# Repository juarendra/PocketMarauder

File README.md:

# PocketMarauder

Perangkat pentest saku: **ESP32-WROOM-32D + OLED 128x64 (SSD1306) + 4 tombol**, berjalan di firmware fork [ESP32Marauder](https://github.com/Spacehuhn/ESP32Marauder) dengan 4 fitur pentest tambahan yang di-build khusus untuk target `POCKET_MARAUDER`.

```
[ OLED 128x64 ]   [ ESP32-WROOM-32D ]
  I2C (IO21/22)     [ A ] [ B ] [ C ] [ D ]   (IO35/32/33/25)
                    Bat: LiPo via TP4056 (IO34)   LED aktif: IO19
```

> **Gambar hardware**: [`docs/images/hardware-placeholder.png`](docs/images/hardware-placeholder.png) — masih placeholder; foto/diagram asli menyusul.

## Fitur

### Firmware bawaan ESP32Marauder (v1.17.0)
- **WiFi** — sniffers (beacon/probe/deauth/EAPOL), scanners (channel analyzer, PineScan, Fox Hunt), attacks (deauth, beacon spam, Karma, Evil Portal, SAE commit, dst.), packet monitor.
- **Bluetooth** — sniffers (BLE scan, FindMy/Airtag, CC skimmer), attacks (Sour Apple, BLE spam, Spoof Airtag).
- **OLED natif** — menu + status bar + persentase baterai, tanpa TFT.
- **Baterai** — ADC IO34 (divider 5.02×), ditampilkan % di status bar.
- **LED aktivitas** — hijau di IO19, menyala saat scan/attack aktif.

### Fitur tambahan (khusus PocketMarauder)
| Fitur | Menu | Fungsi |
|---|---|---|
| **WPS Scan** | WiFi → Sniffers | Pasif: deteksi AP yang mengiklankan WPS, flag `PIN-PRONE` / `LOCKED` |
| **Probe Spam** | WiFi → Attacks | Flood probe request dengan SSID acak |
| **Roam Bait** | WiFi → Attacks | Beacon palsu dengan IE 802.11r (MD) + 802.11k (RM caps) |
| **GATT Explore** | BT → Attacks | Koneksi BLE, enumerasi services/characteristics/values |

Detail penggunaan per fitur: [`docs/USER_MANUAL.md`](docs/USER_MANUAL.md).

## Hardware

| Komponen | Detail |
|---|---|
| MCU | ESP32-WROOM-32D (2.4 GHz WiFi + BLE) |
| Tampilan | SSD1306 OLED 128x64 mono, I2C addr `0x3C` (SDA=IO21, SCL=IO22) |
| Tombol | A=Up (IO35), B=Left/Back (IO32), C=Center/Select (IO33), D=Down (IO25) — active-low, pull-up 10k |
| Baterai | LiPo via charger TP4056 + proteksi; tegangan dibaca IO34 (ADC1_CH6, divider 10k/40.2k) |
| LED | Hijau IO19 (active-low), indikasi aktivitas scan |
| Antena | U.FL — gunakan antena tersambung untuk hasil scan maksimal |

PCB/EAGLE source: [`PCB/EAGLE/`](PCB/EAGLE/).

## Build & Flash

Prasyarat: [PlatformIO](https://platformio.org) CLI + Python 3.

```bash
cd firmware
python -m platformio run -e pocket_marauder        # build (~60 detik)
python -m platformio run -e pocket_marauder -t upload   # flash (butuh USB flasher)
python -m platformio run -e pocket_marauder -t monitor  # serial monitor
```

Build terakhir: **GREEN** — Flash 81.7% (1605679/1966080), RAM 24.9% (81724/327680).

Output: `firmware.bin` (app) + `firmware.factory.bin` (gabungan bootloader + partisi + app).

## Struktur Repo

```
firmware/            firmware (fork ESP32Marauder, target POCKET_MARAUDER)
  esp32_marauder/    source utama
  tools/             build helpers PlatformIO
  installer/         build pipeline installer
PCB/EAGLE/           source PCB (schematic)
docs/
  USER_MANUAL.md     manual pengguna (lengkap)
  images/            simulasi tampilan OLED + placeholder hardware
  plans/             rencana kerja internal
CHANGELOG.md         log perubahan
```

## Lisensi

[GNU GPL v3](LICENSE). Fork dari ESP32Marauder (upstream juga GPLv3).

## Disclaimer

Alat ini untuk **pengujian keamanan yang sah** (lab sendiri, jaringan sendiri, atau dengan izin tertulis pemilik jaringan). Penggunaan di jaringan yang tidak kamu miliki tanpa izin adalah **ilegal** di hampir semua yurisdiksi. Pengguna bertanggung jawab penuh atas perbuatannya.

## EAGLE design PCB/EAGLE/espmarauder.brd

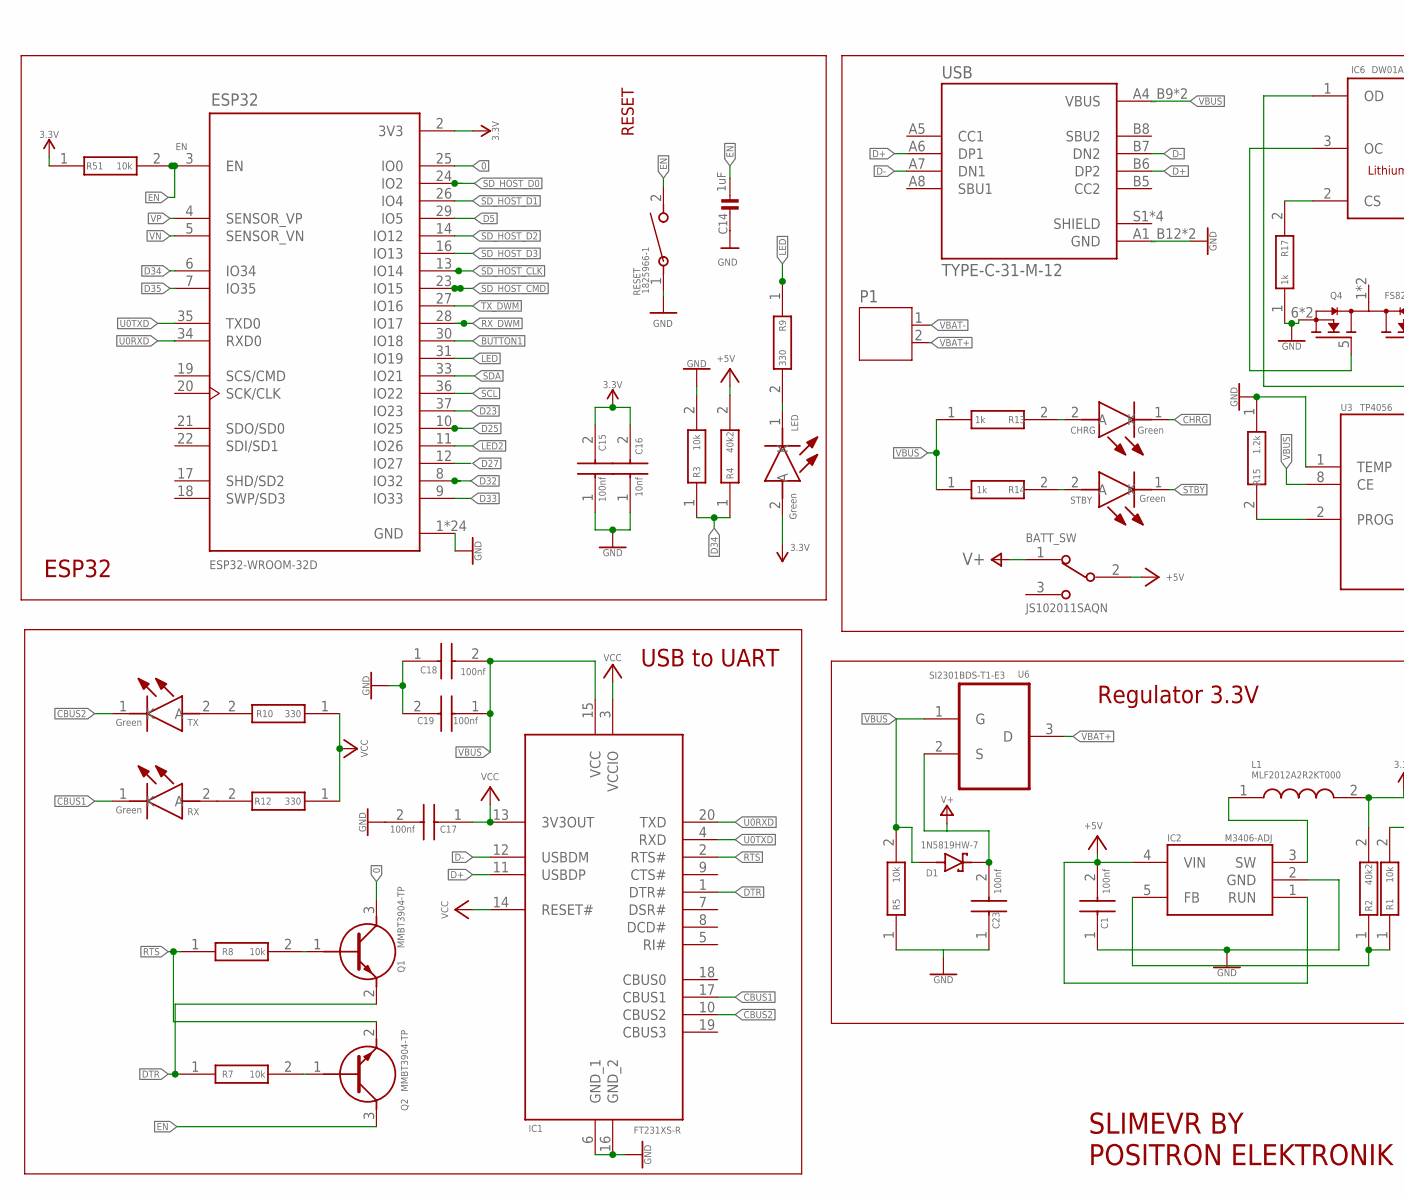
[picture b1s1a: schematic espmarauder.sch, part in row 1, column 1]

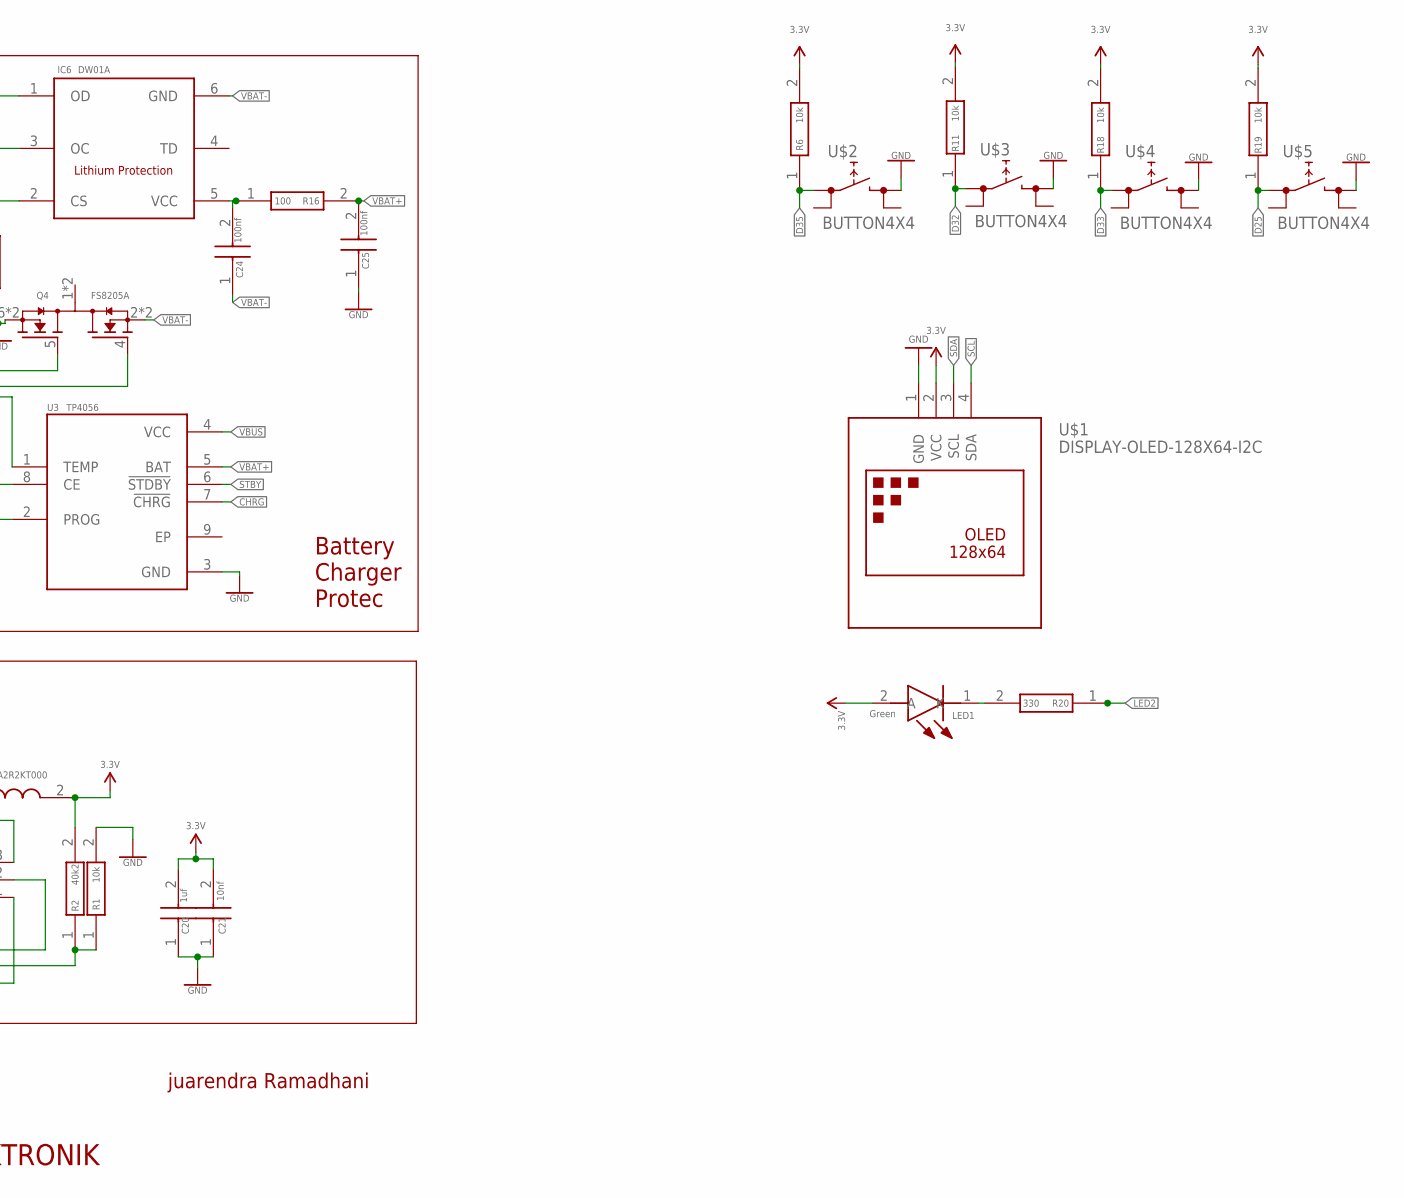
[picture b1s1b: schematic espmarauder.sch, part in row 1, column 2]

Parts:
BATT_SW: JS102011SAQN; SW_JS102011SAQN
C1, C15, C17, C18, C19, C23, C24, C25: 100nf; CAPC1608X87N
C14: 1uF; 0603
C16, C21: 10nf; CAPC1608X87N
C20: 1uf; CAPC1608X87N
CHRG: Green; LEDC2012X80N
D1: 1N5819HW-7; SOD3715X145N
ESP32: ESP32-WROOM-32D; MODULE_ESP32-WROOM-32D
IC1: FT231XS-R; SOP64P599X175-20N
IC2: M3406-ADJ; SOT95P280X100-5N
IC6: DW01A; SOT23-6
L1: MLF2012A2R2KT000; INDC2012X105N
LED, LED1: Green; LEDC2012X80N
P1: JST-PH2
Q1, Q2: MMBT3904-TP; SI2305TP
Q4: FS8205A; SOP65P640X120-8N
R1, R3, R5, R6, R7, R8, R11, R18, R19, R51: 10k; RESC1608X55N
R2, R4: 40k2; RESC1608X55N
R9, R10, R12, R20: 330; ERJH3
R13, R14, R17: 1k; RESC1608X55N
R15: 1.2k; RESC1608X55N
R16: 100; RESC1608X55N
RESET: 1825966-1; SWDIP2_256X170P100
RX: Green; LEDC2012X80N
STBY: Green; LEDC2012X80N
TX: Green; LEDC2012X80N
U3: TP4056; SOP127P600X175-9N
U6: SI2301BDS-T1-E3; SOT95P237X112-3N
U$1: DISPLAY-OLED-128X64-I2C
U$2, U$3, U$4, U$5: BUTTON4X4
USB: TYPE-C-31-M-12; HRO_TYPE-C-31-M-12

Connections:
0: ESP32.25 (IO0), Q1.3 (C)
3.3V: C15.2, C16.2, C20.2, C21.2, ESP32.2 (3V3), L1.2, LED.2 (A), LED1.2 (A), R2.2, R6.2, R11.2, R18.2, R19.2, R51.1, U$1.2 (VCC)
+5V: BATT_SW.2, C1.2, IC2.1 (RUN), IC2.4 (VIN), R4.2
BUTTON1: ESP32.30 (IO18)
CBUS1: IC1.17 (CBUS1), RX.1 (K)
CBUS2: IC1.10 (CBUS2), TX.1 (K)
CHRG: CHRG.1 (K), U3.7 (!CHRG)
D5: ESP32.29 (IO5)
D23: ESP32.37 (IO23)
D25: ESP32.10 (IO25), R19.1, U$5.1
D27: ESP32.12 (IO27)
D32: ESP32.8 (IO32), R11.1, U$3.1
D33: ESP32.9 (IO33), R18.1, U$4.1
D34: ESP32.6 (IO34), R3.1, R4.1
D35: ESP32.7 (IO35), R6.1, U$2.1
D+: IC1.11 (USBDP), USB.A6 (DP1), USB.B6 (DP2)
D-: IC1.12 (USBDM), USB.A7 (DN1), USB.B7 (DN2)
DTR: IC1.1 (DTR#), Q1.2 (E), R7.1
EN: C14.1, ESP32.3 (EN), Q2.3 (C), R51.2, RESET.2
GND: C1.1, C14.2, C15.1, C16.1, C17.2, C18.1, C19.2, C20.1, C21.1, C23.1, C25.1, ESP32.1 (GND), ESP32.15 (GND), ESP32.38 (GND), ESP32.39_1 (GND), ESP32.39_2 (GND), ESP32.39_3 (GND), ESP32.39_4 (GND), ESP32.39_5 (GND), ESP32.39_6 (GND), ESP32.39_7 (GND), ESP32.39_8 (GND), ESP32.39_9 (GND), ESP32.39_10 (GND), ESP32.39_11 (GND), ESP32.39_12 (GND), ESP32.39_13 (GND), ESP32.39_14 (GND), ESP32.39_15 (GND), ESP32.39_16 (GND), ESP32.39_17 (GND), ESP32.39_18 (GND), ESP32.39_19 (GND), ESP32.39_20 (GND), ESP32.39_21 (GND), IC1.6 (GND_1), IC1.16 (GND_2), IC2.2 (GND), Q4.6 (S2), Q4.7 (S2), R1.2, R3.2, R5.1, R15.1, R17.1, RESET.1, U3.1 (TEMP), U3.3 (GND), U$1.1 (GND), U$2.3, U$3.3, U$4.3, U$5.3, USB.A1_B12 (GND), USB.B1_A12 (GND)
LED: ESP32.31 (IO19), R9.1
LED2: ESP32.11 (IO26), R20.1
unnamed: IC2.3 (SW), L1.1
unnamed: LED.1 (K), R9.2
unnamed: IC2.5 (FB), R1.1, R2.1
unnamed: LED1.1 (K), R20.2
unnamed: Q2.1 (B), R7.2
unnamed: Q1.1 (B), R8.2
unnamed: R12.2, RX.2 (A)
unnamed: R10.2, TX.2 (A)
unnamed: CHRG.2 (A), R13.2
unnamed: R14.2, STBY.2 (A)
unnamed: R15.2, U3.2 (PROG)
unnamed: C24.2, IC6.5 (VCC), R16.1
unnamed: IC6.1 (OD), Q4.4 (G1)
unnamed: IC6.2 (CS), R17.2
unnamed: IC6.3 (OC), Q4.5 (G2)
RTS: IC1.2 (RTS#), Q2.2 (E), R8.1
RX_DWM: ESP32.28 (IO17)
SCL: ESP32.36 (IO22), U$1.4 (SDA)
SDA: ESP32.33 (IO21), U$1.3 (SCL)
SD_HOST_CLK: ESP32.13 (IO14)
SD_HOST_CMD: ESP32.23 (IO15)
SD_HOST_D0: ESP32.24 (IO2)
SD_HOST_D1: ESP32.26 (IO4)
SD_HOST_D2: ESP32.14 (IO12)
SD_HOST_D3: ESP32.16 (IO13)
STBY: STBY.1 (K), U3.6 (!STDBY)
TX_DWM: ESP32.27 (IO16)
U0RXD: ESP32.34 (RXD0), IC1.20 (TXD)
U0TXD: ESP32.35 (TXD0), IC1.4 (RXD)
V+: BATT_SW.1, C23.2, D1.C (K), U6.2 (S)
VBAT+: C25.2, P1.2, R16.2, U3.5 (BAT), U6.3 (D)
VBAT-: C24.1, IC6.6 (GND), P1.1, Q4.2 (S1), Q4.3 (S1)
VBUS: C18.2, C19.1, D1.A, IC1.15 (VCC), R5.2, R13.1, R14.1, U3.4 (VCC), U3.8 (CE), U6.1 (G), USB.A4_B9 (VBUS), USB.B4_A9 (VBUS)
VCC: C17.1, IC1.3 (VCCIO), IC1.13 (3V3OUT), IC1.14 (RESET#), R10.1, R12.1
VN: ESP32.5 (SENSOR_VN)
VP: ESP32.4 (SENSOR_VP)

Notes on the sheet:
RESET
ESP32
USB to UART
Battery Charger Protec
Regulator 3.3V
SLIMEVR BY POSITRON ELEKTRONIK
juarendra Ramadhani

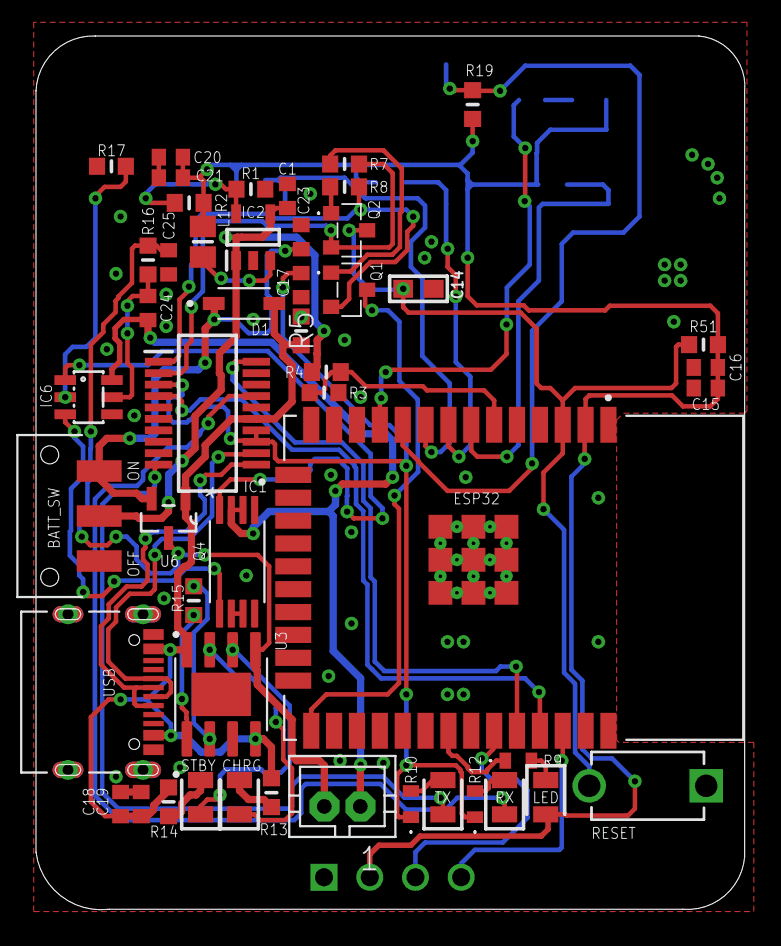
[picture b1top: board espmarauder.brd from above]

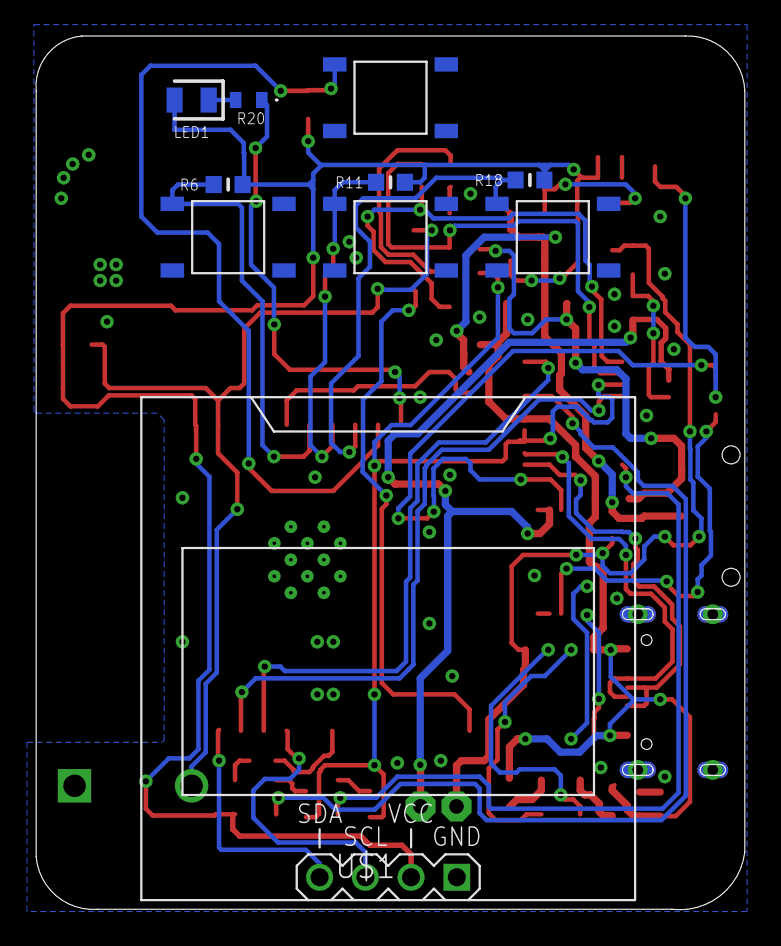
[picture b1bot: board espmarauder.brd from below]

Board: 2 copper layers, 39.4 x 48.5 mm, 59 parts (10 on the bottom side), 44 nets.

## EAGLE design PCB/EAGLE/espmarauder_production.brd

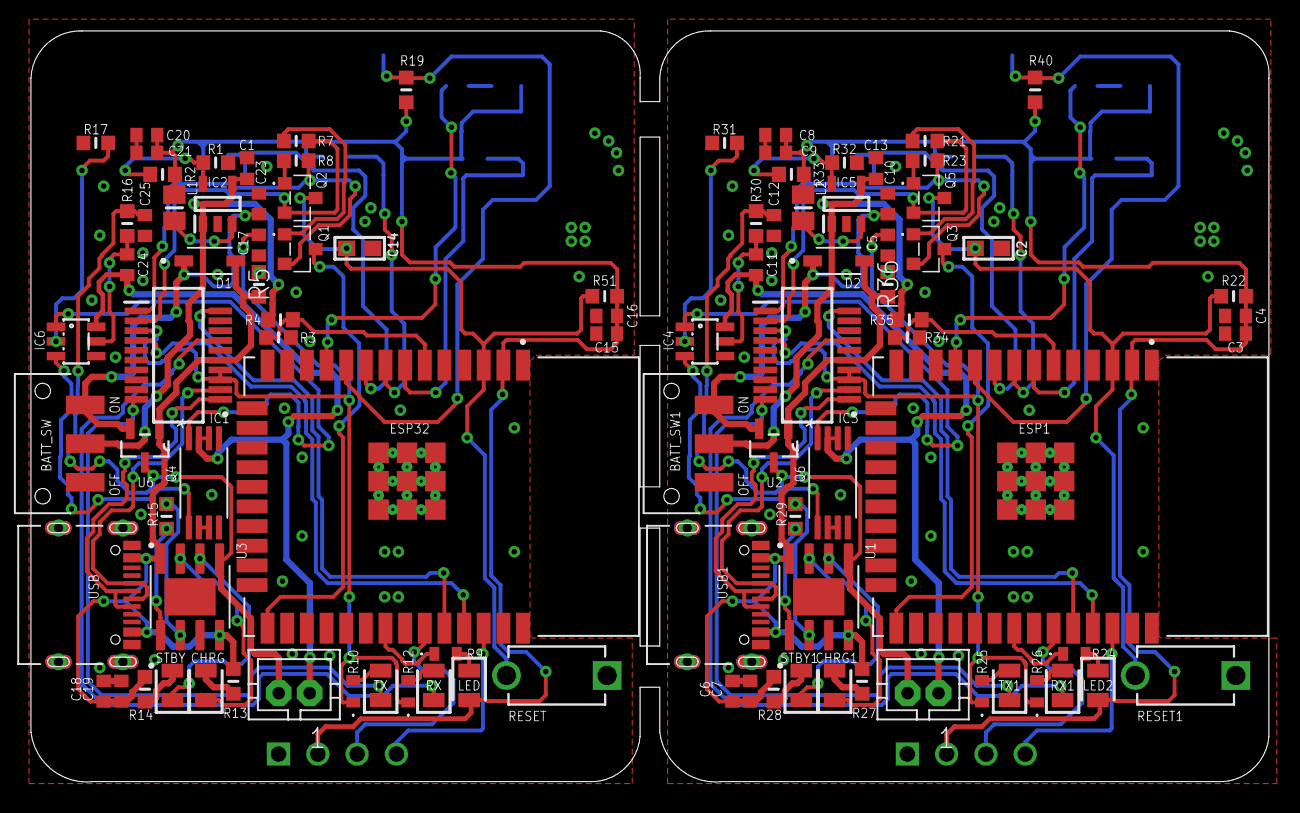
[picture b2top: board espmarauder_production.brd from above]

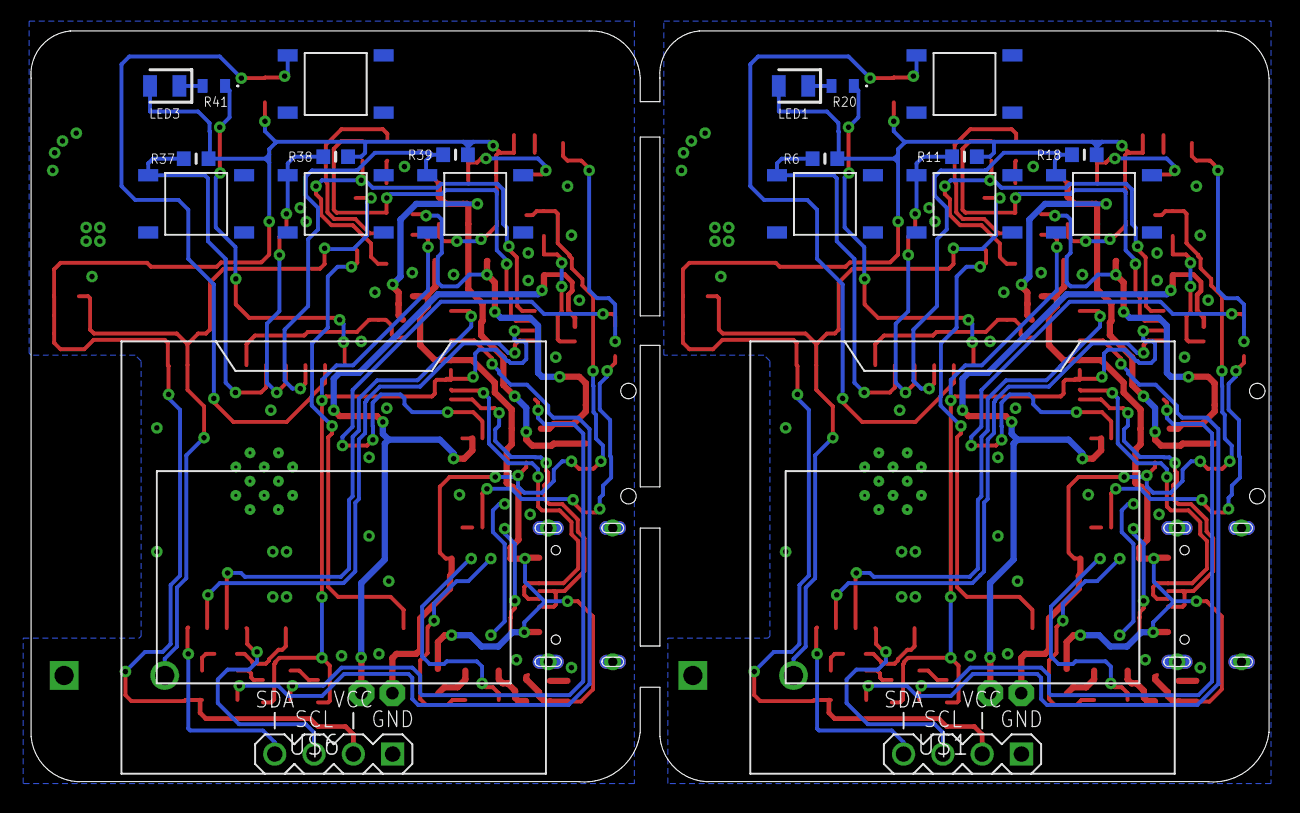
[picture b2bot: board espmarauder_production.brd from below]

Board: 2 copper layers, 80.0 x 48.5 mm, 118 parts (20 on the bottom side), 88 nets.

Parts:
BATT_SW, BATT_SW1: JS102011SAQN; SW_JS102011SAQN
C1, C3, C5, C6, C7, C10, C11, C12, C13, C15, C17, C18, C19, C23, C24, C25: 100nf; CAPC1608X87N
C2, C14: 1uF; 0603
C4, C9, C16, C21: 10nf; CAPC1608X87N
C8, C20: 1uf; CAPC1608X87N
CHRG, CHRG1: Green; LEDC2012X80N
D1, D2: 1N5819HW-7; SOD3715X145N
ESP1, ESP32: ESP32-WROOM-32D; MODULE_ESP32-WROOM-32D
IC1, IC3: FT231XS-R; SOP64P599X175-20N
IC2, IC5: M3406-ADJ; SOT95P280X100-5N
IC4, IC6: DW01A; SOT23-6
L1, L2: MLF2012A2R2KT000; INDC2012X105N
LED, LED1, LED2, LED3: Green; LEDC2012X80N
P1, P2: JST-PH2
Q1, Q2, Q3, Q5: MMBT3904-TP; SI2305TP
Q4, Q6: FS8205A; SOP65P640X120-8N
R1, R3, R5, R6, R7, R8, R11, R18, R19, R21, R22, R23, R32, R34, R36, R37, R38, R39, R40, R51: 10k; RESC1608X55N
R2, R4, R33, R35: 40k2; RESC1608X55N
R9, R10, R12, R20, R24, R25, R26, R41: 330; ERJH3
R13, R14, R17, R27, R28, R31: 1k; RESC1608X55N
R15, R29: 1.2k; RESC1608X55N
R16, R30: 100; RESC1608X55N
RESET, RESET1: 1825966-1; SWDIP2_256X170P100
RX, RX1: Green; LEDC2012X80N
STBY, STBY1: Green; LEDC2012X80N
TX, TX1: Green; LEDC2012X80N
U1, U3: TP4056; SOP127P600X175-9N
U2, U6: SI2301BDS-T1-E3; SOT95P237X112-3N
U$1, U$6: DISPLAY-OLED-128X64-I2C
U$2, U$3, U$4, U$5, U$7, U$8, U$9, U$10: BUTTON4X4
USB, USB1: TYPE-C-31-M-12; HRO_TYPE-C-31-M-12

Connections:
0: ESP32.25, Q1.3
1: ESP1.25, Q3.3
3.3V: C15.2, C16.2, C20.2, C21.2, ESP32.2, L1.2, LED.2, LED1.2, R2.2, R6.2, R11.2, R18.2, R19.2, R51.1, U$1.2
3.3V1: C3.2, C4.2, C8.2, C9.2, ESP1.2, L2.2, LED2.2, LED3.2, R22.1, R33.2, R37.2, R38.2, R39.2, R40.2, U$6.2
+5V: BATT_SW.2, C1.2, IC2.1, IC2.4, R4.2
+5V1: BATT_SW1.2, C13.2, IC5.1, IC5.4, R35.2
CBUS1: IC1.17, RX.1
CBUS2: IC1.10, TX.1
CBUS3: IC3.17, RX1.1
CBUS4: IC3.10, TX1.1
CHRG: CHRG.1, U3.7
CHRG1: CHRG1.1, U1.7
D1: ESP1.6, R34.1, R35.1
D2: ESP1.7, R37.1, U$7.1
D3: ESP1.8, R38.1, U$8.1
D4: ESP1.9, R39.1, U$9.1
D6: ESP1.10, R40.1, U$10.1
D25: ESP32.10, R19.1, U$5.1
D32: ESP32.8, R11.1, U$3.1
D33: ESP32.9, R18.1, U$4.1
D34: ESP32.6, R3.1, R4.1
D35: ESP32.7, R6.1, U$2.1
D+: IC1.11, USB.A6, USB.B6
D+1: IC3.11, USB1.A6, USB1.B6
D-: IC1.12, USB.A7, USB.B7
D-1: IC3.12, USB1.A7, USB1.B7
DTR: IC1.1, Q1.2, R7.1
DTR1: IC3.1, Q3.2, R21.1
EN: C14.1, ESP32.3, Q2.3, R51.2, RESET.2
EN1: C2.1, ESP1.3, Q5.3, R22.2, RESET1.2
GND: C1.1, C14.2, C15.1, C16.1, C17.2, C18.1, C19.2, C20.1, C21.1, C23.1, C25.1, ESP32.1, ESP32.15, ESP32.38, ESP32.39_1, ESP32.39_2, ESP32.39_3, ESP32.39_4, ESP32.39_5, ESP32.39_6, ESP32.39_7, ESP32.39_8, ESP32.39_9, ESP32.39_10, ESP32.39_11, ESP32.39_12, ESP32.39_13, ESP32.39_14, ESP32.39_15, ESP32.39_16, ESP32.39_17, ESP32.39_18, ESP32.39_19, ESP32.39_20, ESP32.39_21, IC1.6, IC1.16, IC2.2, Q4.6, Q4.7, R1.2, R3.2, R5.1, R15.1, R17.1, RESET.1, U3.1, U3.3, U$1.1, U$2.3, U$3.3, U$4.3, U$5.3, USB.A1_B12, USB.B1_A12
GND1: C2.2, C3.1, C4.1, C5.2, C6.1, C7.2, C8.1, C9.1, C10.1, C12.1, C13.1, ESP1.1, ESP1.15, ESP1.38, ESP1.39_1, ESP1.39_2, ESP1.39_3, ESP1.39_4, ESP1.39_5, ESP1.39_6, ESP1.39_7, ESP1.39_8, ESP1.39_9, ESP1.39_10, ESP1.39_11, ESP1.39_12, ESP1.39_13, ESP1.39_14, ESP1.39_15, ESP1.39_16, ESP1.39_17, ESP1.39_18, ESP1.39_19, ESP1.39_20, ESP1.39_21, IC3.6, IC3.16, IC5.2, Q6.6, Q6.7, R29.1, R31.1, R32.2, R34.2, R36.1, RESET1.1, U1.1, U1.3, U$6.1, U$7.3, U$8.3, U$9.3, U$10.3, USB1.A1_B12, USB1.B1_A12
LED: ESP32.31, R9.1
LED1: ESP1.11, R41.1
LED2: ESP32.11, R20.1
LED3: ESP1.31, R24.1
unnamed: IC2.3, L1.1
unnamed: LED.1, R9.2
unnamed: IC2.5, R1.1, R2.1
unnamed: LED1.1, R20.2
unnamed: Q5.1, R21.2
unnamed: Q3.1, R23.2
unnamed: R26.2, RX1.2
unnamed: R25.2, TX1.2
unnamed: Q2.1, R7.2
unnamed: CHRG1.2, R27.2
unnamed: Q1.1, R8.2
unnamed: R12.2, RX.2
unnamed: R10.2, TX.2
unnamed: R28.2, STBY1.2
unnamed: CHRG.2, R13.2
unnamed: R14.2, STBY.2
unnamed: R29.2, U1.2
unnamed: R15.2, U3.2
unnamed: C24.2, IC6.5, R16.1
unnamed: IC6.1, Q4.4
unnamed: IC6.2, R17.2
unnamed: C11.2, IC4.5, R30.1
unnamed: IC4.1, Q6.4
unnamed: IC4.2, R31.2
unnamed: IC4.3, Q6.5
unnamed: IC6.3, Q4.5
unnamed: IC5.3, L2.1
unnamed: IC5.5, R32.1, R33.1
unnamed: LED2.1, R24.2
unnamed: LED3.1, R41.2
RTS: IC1.2, Q2.2, R8.1
RTS1: IC3.2, Q5.2, R23.1
SCL: ESP32.36, U$1.4
SCL1: ESP1.36, U$6.4
SDA: ESP32.33, U$1.3
SDA1: ESP1.33, U$6.3
STBY: STBY.1, U3.6
STBY1: STBY1.1, U1.6
U0RXD: ESP32.34, IC1.20
U0RXD1: ESP1.34, IC3.20
U0TXD: ESP32.35, IC1.4
U0TXD1: ESP1.35, IC3.4
V+: BATT_SW.1, C23.2, D1.C, U6.2
V+1: BATT_SW1.1, C10.2, D2.C, U2.2
VBAT+: C25.2, P1.2, R16.2, U3.5, U6.3
VBAT+1: C12.2, P2.2, R30.2, U1.5, U2.3
VBAT-: C24.1, IC6.6, P1.1, Q4.2, Q4.3
VBAT-1: C11.1, IC4.6, P2.1, Q6.2, Q6.3
VBUS: C18.2, C19.1, D1.A, IC1.15, R5.2, R13.1, R14.1, U3.4, U3.8, U6.1, USB.A4_B9, USB.B4_A9
VBUS1: C6.2, C7.1, D2.A, IC3.15, R27.1, R28.1, R36.2, U1.4, U1.8, U2.1, USB1.A4_B9, USB1.B4_A9
VCC: C17.1, IC1.3, IC1.13, IC1.14, R10.1, R12.1
VCC1: C5.1, IC3.3, IC3.13, IC3.14, R25.1, R26.1

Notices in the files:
parts and their libraries:
microbuilder: This work is placed in the public domain, and may be freely used for commercial and non-commercial work with the following conditions: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
diy-modules: Released under the Creative Commons Attribution 4.0 International License: http://creativecommons.org/licenses/by/4.0
